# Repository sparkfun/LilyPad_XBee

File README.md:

LilyPad XBee
============

[
*LilyPad XBee (DEV-08937)*](https://www.sparkfun.com/products/8937)

The LilyPad Xbee is a breakout board for the popular XBee modules. 
Board includes easy-to-sew tabs and all the necessary power regulation to run on the LilyPad system. 

Repository Contents
-------------------

* **/Hardware** - All Eagle design files (.brd, .sch, .STL)
* **/Production** - Test bed files and production panel files

License Information
-------------------
The hardware is released under [Creative Commons ShareAlike 4.0 International](https://creativecommons.org/licenses/by-sa/4.0/).

Distributed as-is; no warranty is given.

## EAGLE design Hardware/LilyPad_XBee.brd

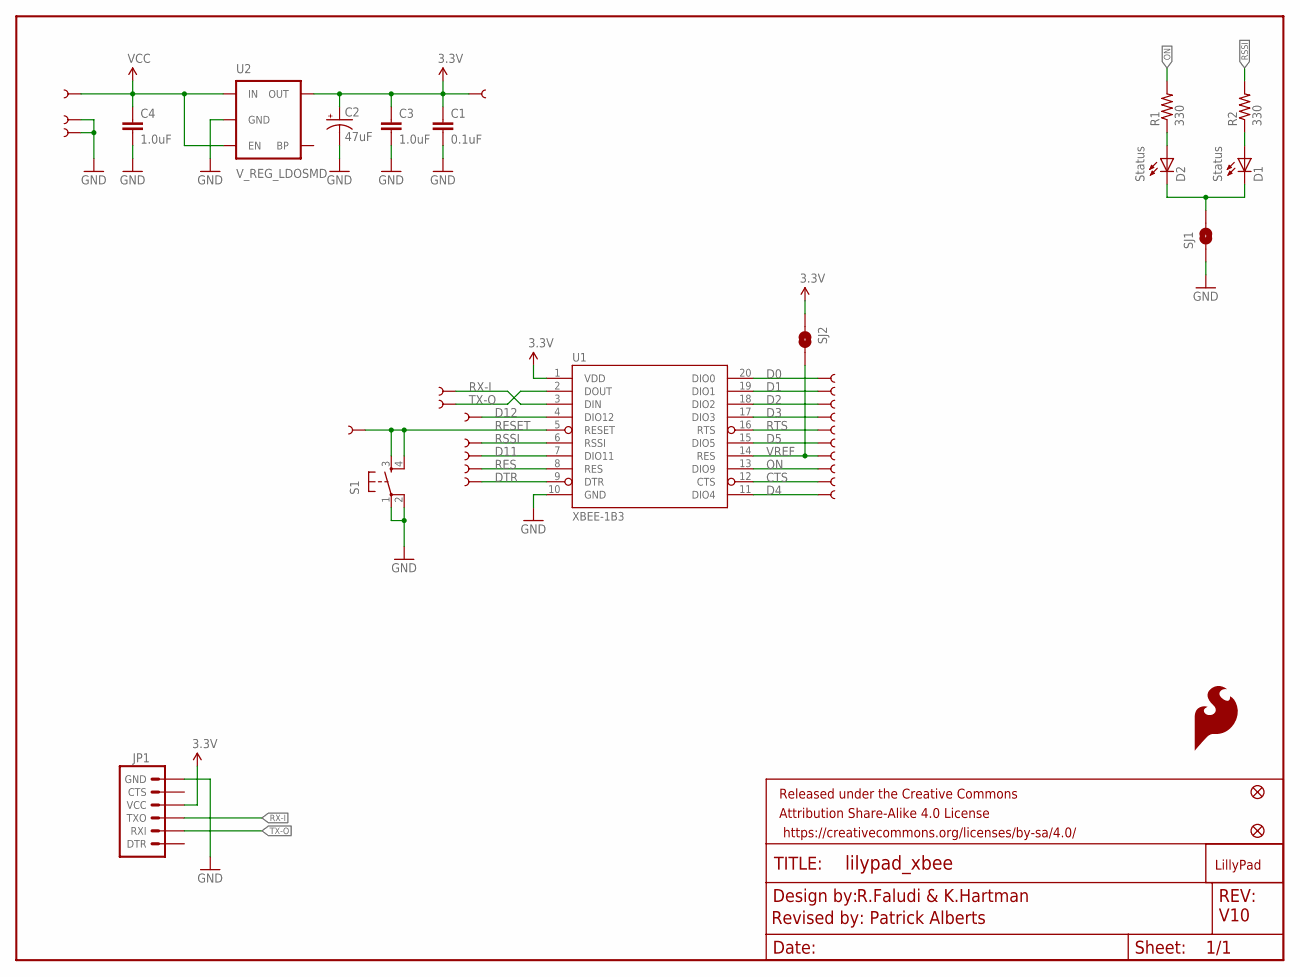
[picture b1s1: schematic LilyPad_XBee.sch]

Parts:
C1: 0.1uF; 0603-CAP
C2: 47uF; EIA3528
C3, C4: 1.0uF; 0603-CAP
D1, D2: Status; LED-0603
FID1, FID2: FIDUCIAL1X2; FIDUCIAL-1X2
FRAME1: FRAME-LETTER; CREATIVE_COMMONS
GND: SEWTAP9; PETAL-LONG-1-2SIDE
JP1: ARDUINO_SERIAL_PROGRAMPTH; 1X06
LOGO1: SFE_LOGO_FLAME.1COP; SFE_LOGO_FLAME_COPPER_.1
R1, R2: 330; 0603-RES
S1: TAC_SWITCHSMD; TACTILE_SWITCH_SMD
SJ1, SJ2: SOLDERJUMPERNC2; SJ_2S-NOTRACE
U1: XBEE-1B3; XBEE-SMD
U2: V_REG_LDOSMD; SOT23-5
U$1: LOGO-LPLP; LOGO-LILYPAD
U$4, U$30, U$31, U$32, U$33, U$34, U$35, U$36, U$37, U$38, U$39, U$40, U$41, U$42, U$43, U$44, U$45, U$46, U$47, U$48, U$51: SEWTAP9; PETAL-LONG-1-2SIDE

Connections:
3.3V: C1.1, C2.A (+), C3.1, JP1.4 (VCC), SJ2.1, U1.1 (VDD), U2.5 (OUT), U$47.1
CTS: U1.12 (CTS), U$38.1
D0: U1.20 (DIO0), U$34.1
D1: U1.19 (DIO1), U$33.1
D2: U1.18 (DIO2), U$32.1
D3: U1.17 (DIO3), U$31.1
D4: U1.11 (DIO4), U$37.1
D5: U1.15 (DIO5), U$4.1
D11: U1.7 (DIO11), U$42.1
D12: U1.4 (DIO12), U$43.1
DTR: U1.9 (DTR), U$48.1
GND: C1.2, C2.C (-), C3.2, C4.2, JP1.6 (GND), S1.1, S1.2, SJ1.1, U1.10 (GND), U2.2 (GND), U$36.1, U$46.1
unnamed: D1.A, R2.1
unnamed: D2.A, R1.1
unnamed: D1.C, D2.C, SJ1.2
ON: R1.2, U1.13 (DIO9), U$39.1
RES: U1.8 (RES), U$41.1
RESET: GND.1, S1.3, S1.4, U1.5 (RESET)
RSSI: R2.2, U1.6 (RSSI), U$51.1
RTS: U1.16 (RTS), U$30.1
RX-I: JP1.3 (TXO), U1.3 (DIN), U$45.1
TX-O: JP1.2 (RXI), U1.2 (DOUT), U$44.1
VCC: C4.1, U2.1 (IN), U2.3 (EN), U$35.1
VREF: SJ2.2, U1.14 (RES), U$40.1

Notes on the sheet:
R.Faludi & K.Hartman
Revised by: Patrick Alberts
V10

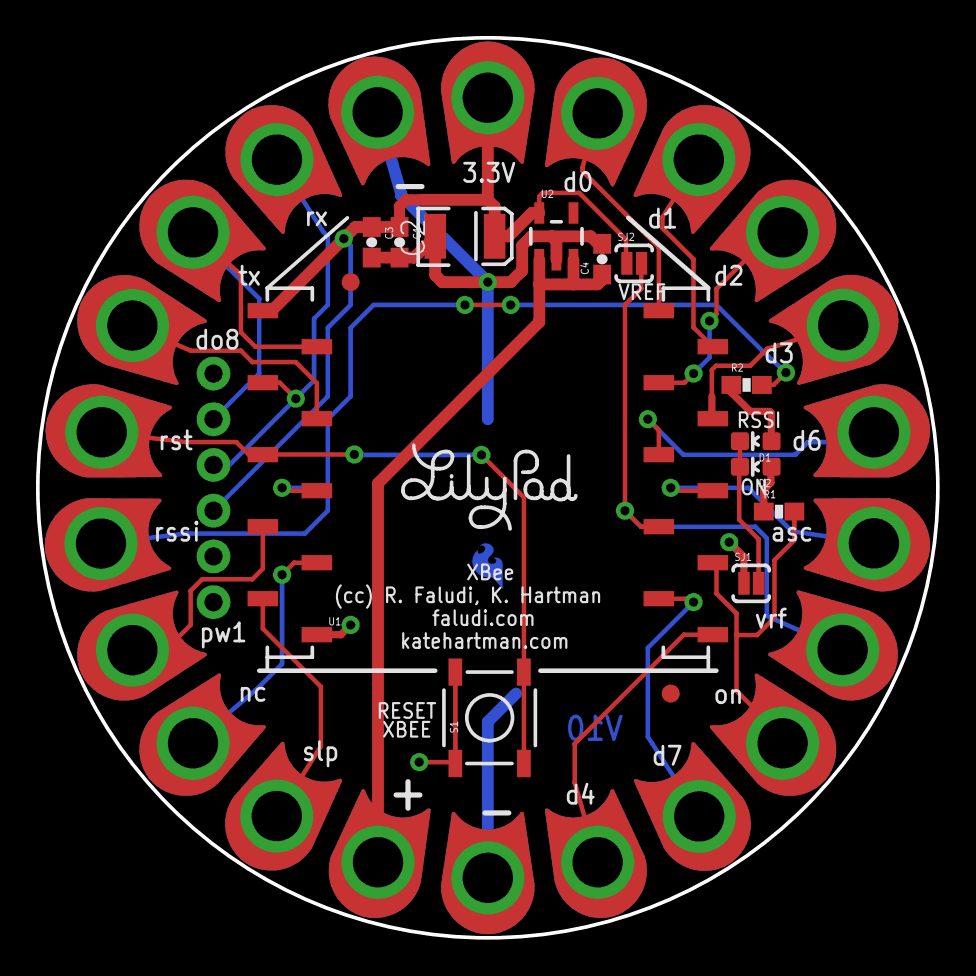
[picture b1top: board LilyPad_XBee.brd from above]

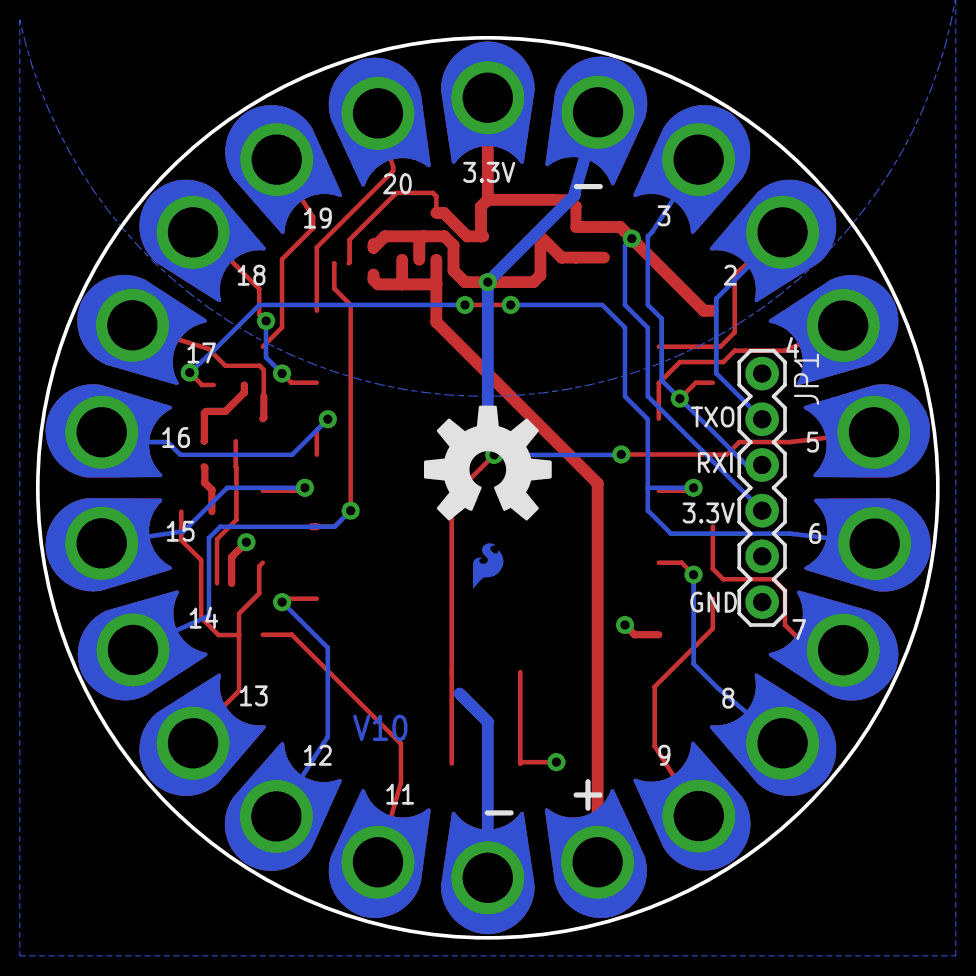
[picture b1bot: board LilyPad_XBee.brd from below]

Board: 2 copper layers, 50.0 x 50.0 mm, 42 parts (3 on the bottom side), 24 nets.

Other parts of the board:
U$2: OSHW-LOGO-L

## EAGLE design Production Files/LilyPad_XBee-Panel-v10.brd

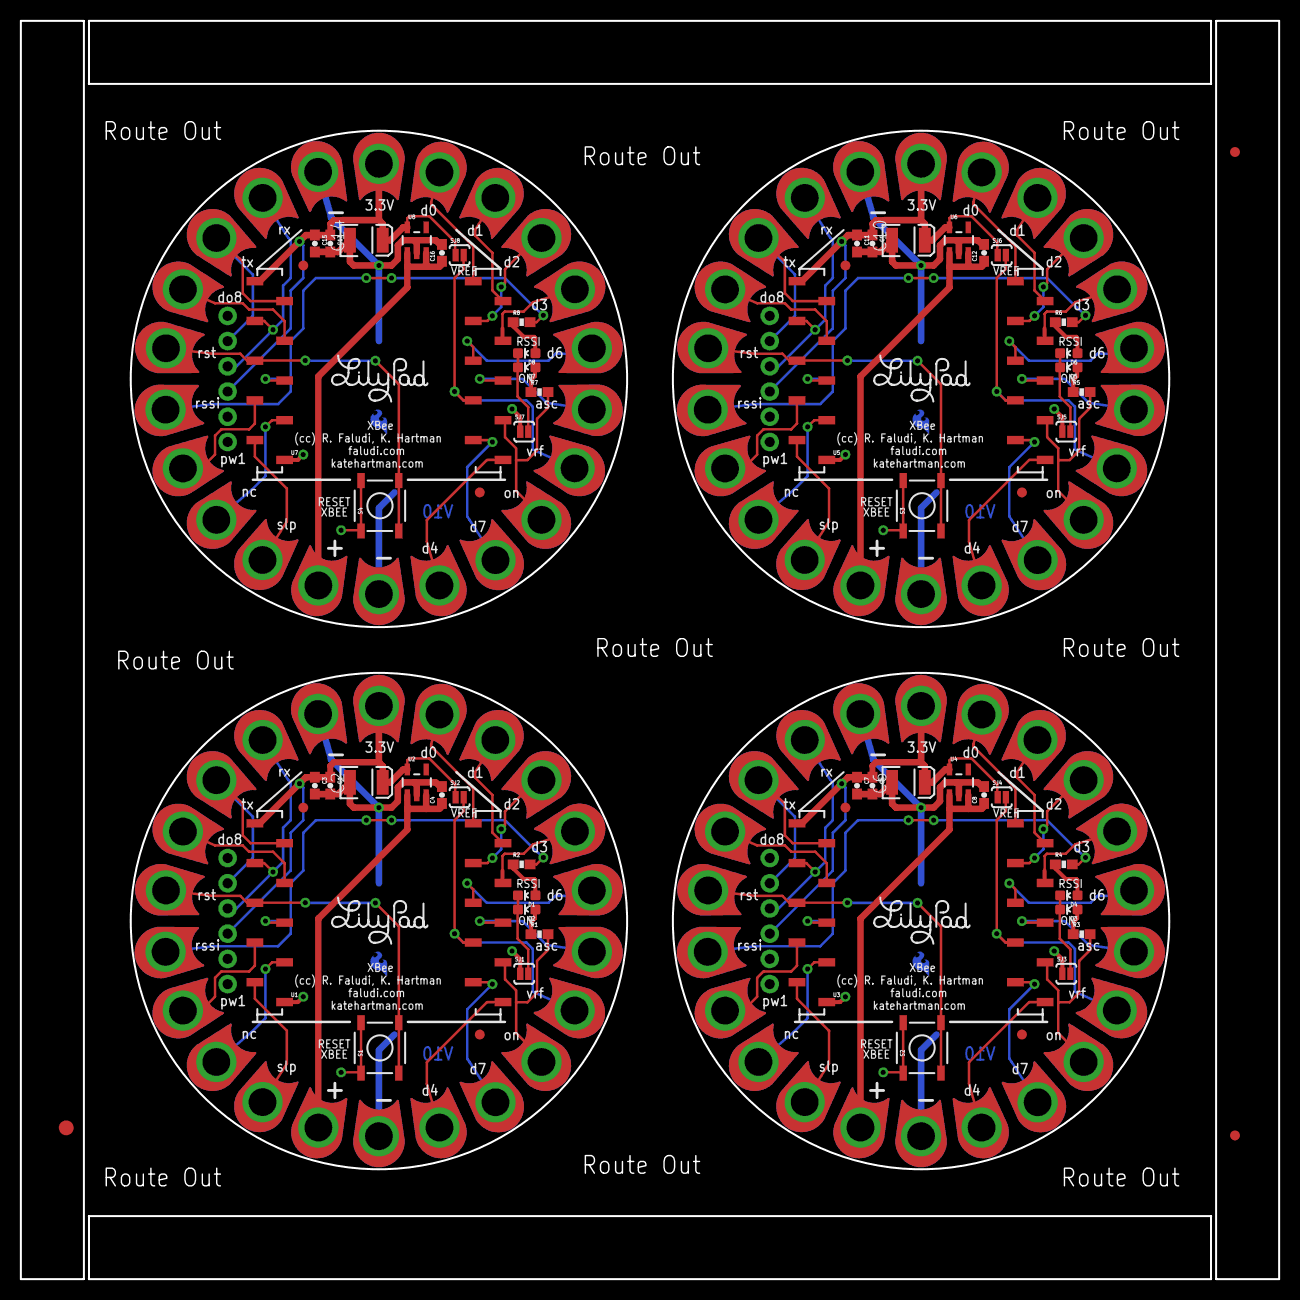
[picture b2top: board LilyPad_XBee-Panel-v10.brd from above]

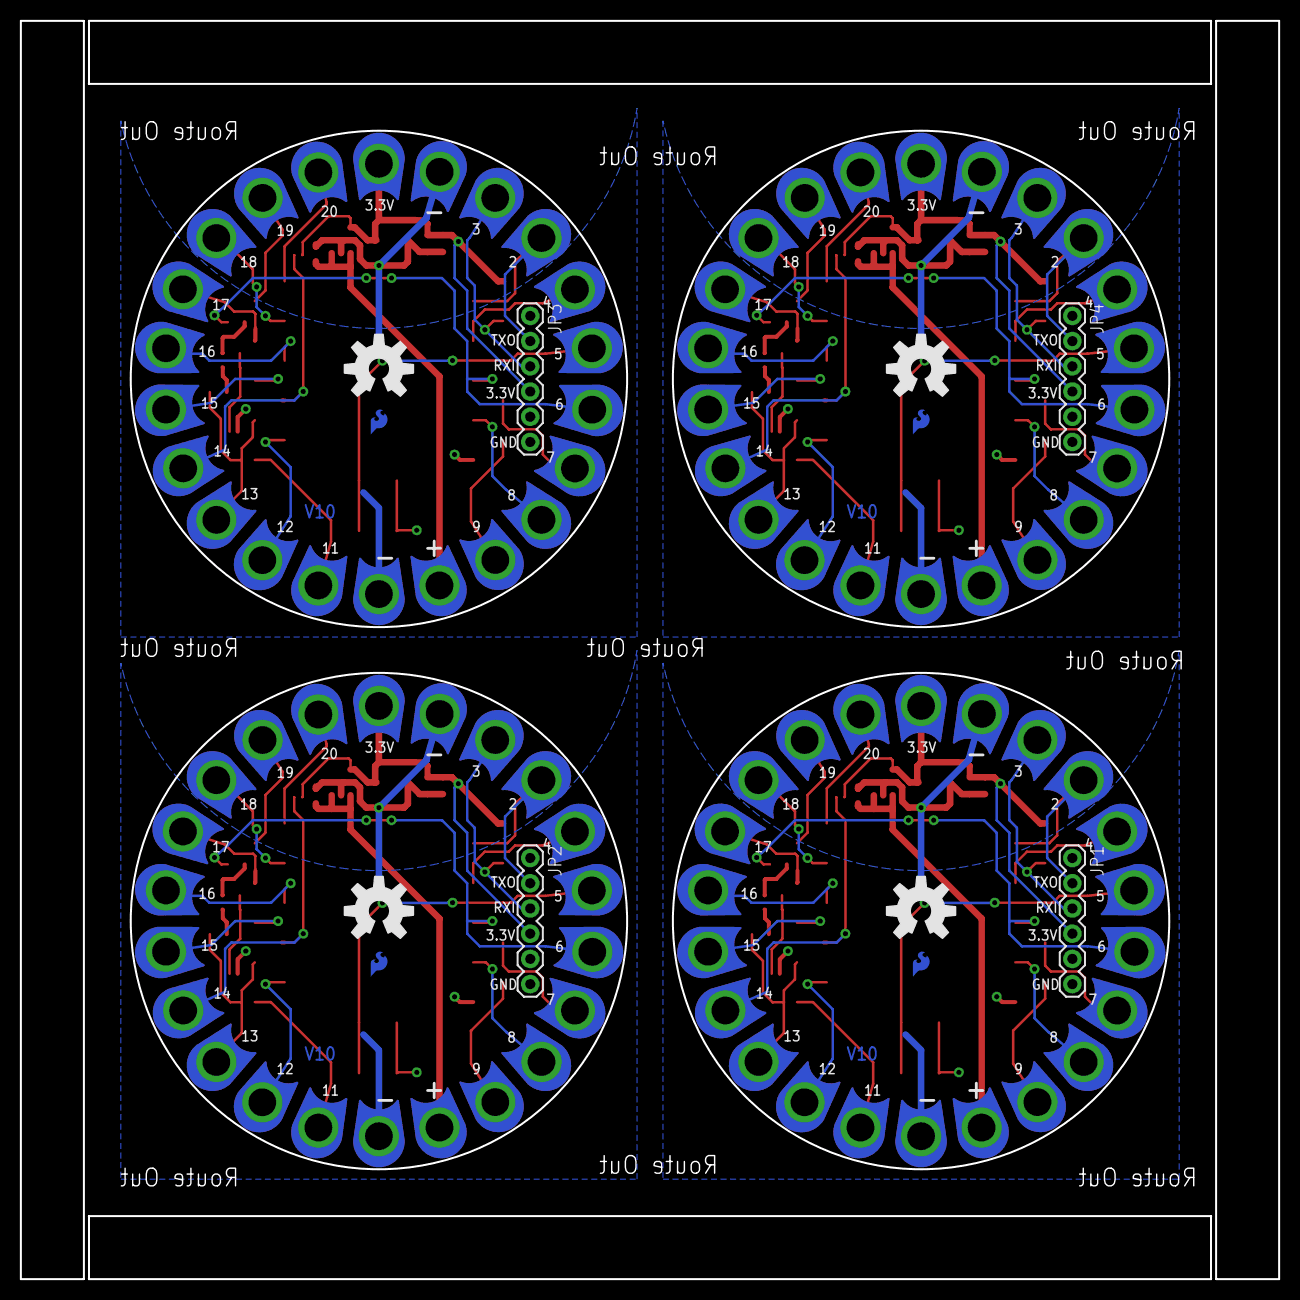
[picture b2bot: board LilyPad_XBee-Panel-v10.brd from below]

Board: 2 copper layers, 126.7 x 126.7 mm, 167 parts (12 on the bottom side), 96 nets.

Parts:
C1, C5, C9, C13: 0.1uF; 0603-CAP
C2, C6, C10, C14: 47uF; EIA3528
C3, C4, C7, C8, C11, C12, C15, C16: 1.0uF; 0603-CAP
D1, D2, D3, D4, D5, D6, D7, D8: Status; LED-0603
E$1: FIDUCIAL-1.5X3
E$4, E$6: FIDUCIAL-1X2
FID1, FID2, FID3, FID4, FID5, FID6, FID7, FID8: FIDUCIAL1X2; FIDUCIAL-1X2
GND, GND1, GND2, GND3: SEWTAP9; PETAL-LONG-1-2SIDE
JP1, JP2, JP3, JP4: 1X06
LOGO1, LOGO2, LOGO3, LOGO4: SFE_LOGO_FLAME.1COP; SFE_LOGO_FLAME_COPPER_.1
R1, R2, R3, R4, R5, R6, R7, R8: 330; 0603-RES
S1, S2, S3, S4: TACTILE_SWITCH_SMD
SJ1, SJ2, SJ3, SJ4, SJ5, SJ6, SJ7, SJ8: SJ_2S-NOTRACE
U1, U3, U5, U7: XBEE-1B3; XBEE-SMD
U2, U4, U6, U8: V_REG_LDOSMD; SOT23-5
U$1, U$25, U$68, U$91: LOGO-LPLP; LOGO-LILYPAD
U$2, U$26, U$69, U$92: OSHW-LOGO-L
U$3, U$4, U$5, U$6, U$7, U$8, U$9, U$10, U$11, U$12, U$13, U$14, U$15, U$16, U$17, U$18, U$19, U$20, U$21, U$22, U$23, U$24, U$27, U$28, U$29, U$30, U$31, U$32, U$33, U$34, U$35, U$36, U$37, U$38, U$39, U$40, U$41, U$42, U$43, U$44, U$45, U$46, U$47, U$48, U$49, U$50, U$51, U$52, U$53, U$54, U$55, U$56, U$57, U$58, U$59, U$60, U$61, U$62, U$63, U$64, U$65, U$66, U$67, U$70, U$71, U$72, U$73, U$74, U$75, U$76, U$77, U$78, U$79, U$80, U$81, U$82, U$83, U$84, U$85, U$86, U$87, U$88, U$89, U$90: SEWTAP9; PETAL-LONG-1-2SIDE

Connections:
3.3V: C1.1, C2.A, C3.1, JP1.4, SJ2.1, U1.1, U2.5, U$47.1
3.3V1: C5.1, C6.A, C7.1, JP2.4, SJ4.1, U3.1, U4.5, U$21.1
3.3V2: C9.1, C10.A, C11.1, JP3.4, SJ6.1, U5.1, U6.5, U$64.1
3.3V3: C13.1, C14.A, C15.1, JP4.4, SJ8.1, U7.1, U8.5, U$87.1
CTS: U1.12, U$38.1
CTS1: U3.12, U$12.1
CTS2: U5.12, U$55.1
CTS3: U7.12, U$78.1
D0: U1.20, U$34.1
D1: U1.19, U$33.1
D2: U1.18, U$32.1
D3: U1.17, U$31.1
D4: U1.11, U$37.1
D5: U1.15, U$4.1
D6: U3.4, U$17.1
D7: U3.7, U$16.1
D8: U3.11, U$11.1
D9: U3.15, U$24.1
D10: U3.17, U$5.1
D11: U1.7, U$42.1
D12: U1.4, U$43.1
D13: U3.18, U$6.1
D14: U3.19, U$7.1
D15: U3.20, U$8.1
D16: U5.4, U$60.1
D17: U5.7, U$59.1
D18: U5.11, U$54.1
D19: U5.15, U$67.1
D20: U5.17, U$28.1
D21: U5.18, U$29.1
D22: U5.19, U$49.1
D23: U5.20, U$50.1
D24: U7.4, U$83.1
D25: U7.7, U$82.1
D26: U7.11, U$77.1
D27: U7.15, U$90.1
D28: U7.17, U$71.1
D29: U7.18, U$72.1
D30: U7.19, U$73.1
D31: U7.20, U$74.1
DTR: U1.9, U$48.1
DTR1: U3.9, U$22.1
DTR2: U5.9, U$65.1
DTR3: U7.9, U$88.1
GND: C1.2, C2.C, C3.2, C4.2, JP1.6, S1.1, S1.2, SJ1.1, U1.10, U2.2, U$36.1, U$46.1
GND1: C5.2, C6.C, C7.2, C8.2, JP2.6, S2.1, S2.2, SJ3.1, U3.10, U4.2, U$10.1, U$20.1
GND2: C9.2, C10.C, C11.2, C12.2, JP3.6, S3.1, S3.2, SJ5.1, U5.10, U6.2, U$53.1, U$63.1
GND3: C13.2, C14.C, C15.2, C16.2, JP4.6, S4.1, S4.2, SJ7.1, U7.10, U8.2, U$76.1, U$86.1
unnamed: D1.A, R2.1
unnamed: D2.A, R1.1
unnamed: D1.C, D2.C, SJ1.2
unnamed: D3.A, R3.1
unnamed: D4.A, R4.1
unnamed: D3.C, D4.C, SJ3.2
unnamed: D5.A, R5.1
unnamed: D6.A, R6.1
unnamed: D5.C, D6.C, SJ5.2
unnamed: D7.A, R7.1
unnamed: D8.A, R8.1
unnamed: D7.C, D8.C, SJ7.2
ON: R1.2, U1.13, U$39.1
ON1: R3.2, U3.13, U$13.1
ON2: R5.2, U5.13, U$56.1
ON3: R7.2, U7.13, U$79.1
RES: U1.8, U$41.1
RES1: U3.8, U$15.1
RES2: U5.8, U$58.1
RES3: U7.8, U$81.1
RESET: GND.1, S1.3, S1.4, U1.5
RESET1: GND1.1, S2.3, S2.4, U3.5
RESET2: GND2.1, S3.3, S3.4, U5.5
RESET3: GND3.1, S4.3, S4.4, U7.5
RSSI: R2.2, U1.6, U$51.1
RSSI1: R4.2, U3.6, U$23.1
RSSI2: R6.2, U5.6, U$66.1
RSSI3: R8.2, U7.6, U$89.1
RTS: U1.16, U$30.1
RTS1: U3.16, U$3.1
RTS2: U5.16, U$27.1
RTS3: U7.16, U$70.1
RX-I: JP1.3, U1.3, U$45.1
RX-I1: JP2.3, U3.3, U$19.1
RX-I2: JP3.3, U5.3, U$62.1
RX-I3: JP4.3, U7.3, U$85.1
TX-O: JP1.2, U1.2, U$44.1
TX-O1: JP2.2, U3.2, U$18.1
TX-O2: JP3.2, U5.2, U$61.1
TX-O3: JP4.2, U7.2, U$84.1
VCC: C4.1, U2.1, U2.3, U$35.1
VCC1: C8.1, U4.1, U4.3, U$9.1
VCC2: C12.1, U6.1, U6.3, U$52.1
VCC3: C16.1, U8.1, U8.3, U$75.1
VREF: SJ2.2, U1.14, U$40.1
VREF1: SJ4.2, U3.14, U$14.1
VREF2: SJ6.2, U5.14, U$57.1
VREF3: SJ8.2, U7.14, U$80.1

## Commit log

2014-03-18 Initial Commit
    with brd/sch
2014-03-19 Reset Switch / Jumper Redo/ 0603
    Added a reset switch, updated the jumpers, oshw logo, and 0603
2014-03-24 Added Silk / re arranged LED Resistors
2014-03-27 Added Copper Flame/ Silk for jumper
2014-04-01 Fixed Silk
2014-04-18 Added fiducials
2014-04-18 created panel v10
2014-08-07 Adding in current board files
2014-08-07 Adding back in revision 1.0 files

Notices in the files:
parts and their libraries:
SparkFun-Capacitors: Licensing: Creative Commons ShareAlike 4.0 International - https://creativecommons.org/licenses/by-sa/4.0
SparkFun-Aesthetics: Released under the Creative Commons Attribution Share-Alike 4.0 License
SparkFun-Aesthetics: Released under the Creative Commons
